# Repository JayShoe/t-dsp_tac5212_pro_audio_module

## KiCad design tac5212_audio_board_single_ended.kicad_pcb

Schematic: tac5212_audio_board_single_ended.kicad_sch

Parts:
3V108, 5V108: jumper; jumper_slice_1mm; not fitted
ADD108: 0x50 | 0xA0; SolderJumper-2_Open_Pad0.5x1.0mm_ADDR; not fitted
ADD110: 0x52 | 0xA4; SolderJumper-2_Open_Pad0.5x1.0mm_ADDR; not fitted
ADD111: 0x53 | 0xA6; SolderJumper-2_Open_Pad0.5x1.0mm_ADDR; not fitted
ADD112: 0x51 | 0xA2; SolderJumper-2_Open_Pad0.5x1.0mm_ADDR; not fitted
C108, C111, C115: 10uF; C_0805_2012Metric_Pad1.18x1.45mm_HandSolder; LCSC C2182156
C109, C112, C116: 0.1uF; C_0402_1005Metric; LCSC C106994
C110, C117, C121, C123: 47uF; CP_EIA-3528-21_Kemet-B_Pad1.50x2.35mm_HandSolder; LCSC C284844; not fitted
C113, C114, C120, C122: 0.0047µF (4.7nF); C_0603_1608Metric_Pad1.08x0.95mm_HandSolder; LCSC C1870901
C118, C119, C128: 1uF; C_0603_1608Metric_Pad1.08x0.95mm_HandSolder; LCSC C2172920
C124: 10UF confirm polarity; C_0603_1608Metric_Pad1.08x0.95mm_HandSolder; LCSC C2167896
C125, C126, C127: 10UF; C_0603_1608Metric_Pad1.08x0.95mm_HandSolder; LCSC C2167896
C129: 1uF (IS THIS TOO MUCH?); C_0603_1608Metric_Pad1.08x0.95mm_HandSolder; LCSC C2172920
C130, C131: 47uF; C_0805_2012Metric_Pad1.15x1.40mm_HandSolder; LCSC C16780
D108, D109, D110, D111, D112: TPD1E10B06; D_0402_1005Metric_Pad0.77x0.64mm_HandSolder; LCSC C48260
D113, D114, D115: TPD1E1B04 - 0402 size; D_0402_1005Metric_Pad0.77x0.64mm_HandSolder; LCSC C48260
D116: RED LED; D_0805_2012Metric_custom; LCSC C94868
DOUT108: Jump DOUT1; jumper_slice_disconnected_alt-text; not fitted
E108, E109: jumper; jumper_slice; not fitted
FB108, FB109, FB110, FB111: BLM21A601S - BLM21AG601SH1; C_0805_2012Metric_Pad1.18x1.45mm_HandSolder_alt_location; LCSC C437406
G108, G109, G110, G111, G112, G113, G114, G115, G116: VIA; via; not fitted
G117, G118: jumper; jumper_slice; not fitted
G119: jumper; jumper_slice_alt1; not fitted
GND108: BRIDGE; jumper_slice; not fitted
MCLK108: jumper; SolderJumper-2_P1.3mm_Open_Pad1.0x1.5mm; not fitted
NT108, NT109: NetTie_2; NetTie-2_SMD_Pad0.2mm
PU_EN108: JUMPER; SolderJumper-2_Open_Pad0.5x1.0mm_PU; not fitted
R108, R111, R132, R135: 10 ohm; C_0603_1608Metric_Pad1.08x0.95mm_HandSolder
R109, R127, R131, R134: DNP; C_0603_1608Metric_Pad1.08x0.95mm_HandSolder; not fitted
R110, R112, R113, R114, R115, R118, R119: 0 Ohm; R_0402_1005Metric_Pad0.72x0.64mm_HandSolder; LCSC C242160
R116, R129, R133, R136: 0 ohm; C_0603_1608Metric_Pad1.08x0.95mm_HandSolder
R117, R125: 27 ohm; R_0402_1005Metric_Pad0.72x0.64mm_HandSolder
R120, R121, R128: 2.21k ohm; R_0402_1005Metric; LCSC C138019
R122: 22.0k; R_0402_1005Metric; LCSC C82868
R123, R124: 4.7k; R_0402_1005Metric; LCSC C278641
R126: 2.21k ohm; R_0402_1005Metric; LCSC C60491
R130, R137, R138, R139: 100K; C_0603_1608Metric_Pad1.08x0.95mm_HandSolder
SCL108: jumper; jumper_slice; not fitted
SCL109: jumper; R_0402_1005Metric_Pad0.72x0.64mm_HandSolder; not fitted
SDA108: jumper; jumper_slice; not fitted
T108, T109, T110, T111: Tab
T*C108, T*C110: 10uF; C_0805_2012Metric_Pad1.18x1.45mm_HandSolder; LCSC C2182156
T*C109: 1uF; C_0603_1608Metric_Pad1.08x0.95mm_HandSolder; LCSC C2172920
TAC108-Q1: TAC5212-Q1; Texas_RHB0032E_VQFN-32-1EP_5x5mm_P0.5mm_EP3.45x3.45mm_Therm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; not fitted
TAC5212: TAC5212; VQFN-24-1EP_4x4mm_P0.5mm_EP2.45x2.45mm_ThermalVias; LCSC C44853694
U108: Single Buffer with Tri-state Passthru - SN74LVC1G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; SOT-23-5
U109: 3.3v LDO - TLV74133PDBVR; SOT-23-5; LCSC C471862
board_outline108: board; audio_module_board_outline_50x34.5_d1; not fitted

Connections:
3.3V_A: 3V108.2, T*C110.1, U109.5 (OUT)
3.3V_LDO: 3V108.1, NT109.1, R122.2, R123.2, R126.1, board_outline108.46 (3.3V)
3.3V_THIN: C108.1, C109.1, NT109.2, TAC108-Q1.31 (AVDD), TAC5212.23 (AVDD)
3.3v_IDE: C111.1, C112.1, C128.1, C131.1, PU_EN108.2, SCL109.2, TAC108-Q1.7 (IOVDD), TAC5212.6 (IOVDD), U108.4 (OE^), U108.5 (VCC), board_outline108.4 (GNDD)
5V: 5V108.1, C130.1, NT108.1, board_outline108.45 (5V)
5212_BCLK1: R119.1, board_outline108.11 (BCLK)
5212_DIN1: R118.1, board_outline108.7 (DSP_DOUT)
5212_DOUT1: DOUT108.1, R117.1, U108.1 (A)
5212_DOUT1+: DOUT108.2, R125.1, board_outline108.9 (DSP_DIN)
5212_LRCK1: R115.1, board_outline108.13 (LRCK)
5212_MCLK1: MCLK108.1, board_outline108.19 (MCLK)
5212_SCL: R121.1, SCL108.2, TAC108-Q1.9 (SCL), TAC5212.7 (SCL), board_outline108.37 (SCL)
5212_SDA: R120.1, SDA108.2, TAC108-Q1.10 (SDA), TAC5212.8 (SDA), board_outline108.38 (SDA)
DSP_SCL: SCL108.1, board_outline108.17 (SCL)
DSP_SDA: SDA108.1, board_outline108.15 (SDA)
EN_HELD_HIGH: C129.1, R128.1, U109.3 (EN), board_outline108.1 (HELD_HIGH)
Earth: C108.2, C109.2, C113.2, C114.2, C118.2, C119.1, C120.2, C122.2, D108.2 (K), D109.2 (K), D110.2 (K), D111.2 (K), D112.2 (K), D113.2 (K), D114.2 (K), D115.2 (K), E108.1, E109.1, G108.1, G109.1, G110.1, G111.1, G112.1, G113.1, G114.1, G115.1, G116.1, G119.1, GND108.1, R130.2, R137.2, R138.2, R139.2, board_outline108.22 (AGND), board_outline108.24 (AGND), board_outline108.26 (AGND), board_outline108.28 (AGND), board_outline108.30 (AGND), board_outline108.32 (AGND), board_outline108.34 (AGND), board_outline108.36 (AGND)
GNDD: ADD108.1, C111.2, C112.2, C115.2, C116.2, C128.2, C129.2, C130.2, C131.2, D116.1 (K), G117.2, G118.2, GND108.2, R124.2, TAC108-Q1.1 (VSS), TAC108-Q1.8 (IOVSS), TAC108-Q1.15 (BSTVSS), TAC108-Q1.26 (AVSS), TAC108-Q1.33 (VSS), TAC5212.25 (VSS), TAC5212.A1 (VSS), TAC5212.A2 (VSS), TAC5212.A3 (VSS), TAC5212.A4 (VSS), U108.3 (GND), board_outline108.6 (GNDD), board_outline108.8 (GNDD), board_outline108.10 (GNDD), board_outline108.12 (GNDD), board_outline108.14 (GNDD), board_outline108.16 (GNDD), board_outline108.18 (GNDD), board_outline108.20 (GNDD), board_outline108.39 (GNDD), board_outline108.44 (GNDD), board_outline108.47 (GNDD)
GPI1: MCLK108.2, R110.1, board_outline108.43 (GPI1)
GPIO1: R114.1, board_outline108.40 (GPIO1)
GPIO2: R113.1, board_outline108.41 (GPIO2)
GPO1: R112.1, board_outline108.42 (GPO1)
IN1M: C126.2, TAC108-Q1.19 (IN1M), TAC5212.16 (IN1M)
IN1M+: D114.1 (K), FB110.1, board_outline108.31 (IN1M)
IN1P: C127.2, TAC108-Q1.18 (IN1P), TAC5212.15 (IN1P)
IN1P+: D115.1 (K), FB111.1, board_outline108.29 (IN1P)
IN2M: C124.2, TAC108-Q1.21 (IN2M), TAC5212.18 (IN2M)
IN2M+: D112.1 (K), FB108.1, board_outline108.35 (IN2M)
IN2P: C125.2, TAC108-Q1.20 (IN2P), TAC5212.17 (IN2P)
IN2P+: D113.1 (K), FB109.1, board_outline108.33 (IN2P)
MICBIAS: C118.1, TAC108-Q1.17 (MICBIAS), TAC5212.14 (MICBIAS), board_outline108.48 (MIC_BIAS)
unnamed: 5V108.2, board_outline108.3 (5V)
unnamed: ADD110.1, R122.1
unnamed: ADD111.1, R123.1
unnamed: ADD112.1, R124.1
unnamed: C110.1, C113.1, R108.1, R127.1, R129.2
unnamed: C114.1, C117.1, R109.1, R111.1, R116.2
unnamed: C120.1, C121.1, R131.1, R132.1, R133.2
unnamed: C122.1, C123.1, R134.1, R135.1, R136.2
unnamed: C124.1, FB108.2, R130.1
unnamed: C125.1, FB109.2, R137.1
unnamed: C126.1, FB110.2, R138.1
unnamed: C127.1, FB111.2, R139.1
unnamed: D116.2 (A), R126.2
unnamed: E108.2, board_outline108.49 (AGND)
unnamed: E109.2, board_outline108.50 (AGND)
unnamed: G117.1, board_outline108.51 (DGND)
unnamed: G118.1, board_outline108.52 (DGND)
unnamed: PU_EN108.1, R120.2, R121.2
unnamed: R128.2, SCL109.1
unnamed: ADD108.2, ADD110.2, ADD111.2, ADD112.2, TAC108-Q1.22 (ADDRA), TAC5212.13 (ADDR)
unnamed: R119.2, TAC108-Q1.3 (BCLK), TAC5212.2 (BCLK)
unnamed: R118.2, TAC108-Q1.6 (DIN), TAC5212.5 (DIN)
unnamed: R117.2, TAC108-Q1.5 (DOUT), TAC5212.4 (DOUT)
unnamed: C115.1, C116.1, TAC108-Q1.2 (DREG), TAC5212.1 (DREG)
unnamed: R115.2, TAC108-Q1.4 (FSYNC), TAC5212.3 (FSYNC)
unnamed: R110.2, TAC108-Q1.25 (GPI1A), TAC5212.12 (GPI1)
unnamed: R114.2, TAC108-Q1.11 (GPIO1), TAC5212.9 (GPIO1)
unnamed: R113.2, TAC108-Q1.24 (GPI2A), TAC5212.10 (GPIO2)
unnamed: R112.2, TAC108-Q1.23 (GPO1A), TAC5212.11 (GPO1)
unnamed: C119.2, TAC108-Q1.32 (VREF), TAC5212.24 (VREF)
unnamed: R125.2, U108.2 (B)
unnamed: G119.2, T*C108.2, T*C109.2, T*C110.2, U109.2 (GND)
unnamed: NT108.2, T*C108.1, T*C109.1, U109.1 (IN)
OUT1M: TAC108-Q1.27 (OUT1M), TAC5212.19 (OUT1M)
OUT1M+: C110.2, D108.1 (K), R129.1, board_outline108.23 (OUT1M)
OUT1P: R108.2, R109.2, R111.2, R127.2, R131.2, R132.2, R134.2, R135.2, TAC108-Q1.28 (OUT1P), TAC5212.20 (OUT1P)
OUT1P+: C117.2, D109.1 (K), R116.1, board_outline108.21 (OUTP)
OUT2M: TAC108-Q1.30 (OUT2M), TAC5212.22 (OUT2M)
OUT2M+: C123.2, D111.1 (K), R136.1, board_outline108.27 (OUT2M)
OUT2P: TAC108-Q1.29 (OUT2P), TAC5212.21 (OUT2P)
OUT2P+: C121.2, D110.1 (K), R133.1, board_outline108.25 (OUT2P)

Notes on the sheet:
AUDIO FILTERS
TAC5212 AUDIO CODEC
POWER SUPPLY
MODULE IO
# TAC5212 Audio Module - Input/Output Interface Documentation ## Document Control | Version | Date | Author | Changes | |---------|------|--------|---------| | 1.0 | [Date] | [Name] | Initial release | --- ## Module Overview The TAC5212 audio module provides flexible, high-quality audio input and o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
REPLACE WITH ANALOG BUFFER SUCH AS SN74LVC1G66 SO THERE IS NO CONTENTION BETWEEN THE SUB-MODULES!
DATA OUTPUT BUFFER
TAC5212 AUDIO BREAKOUT MODULE
POWER INDICATOR

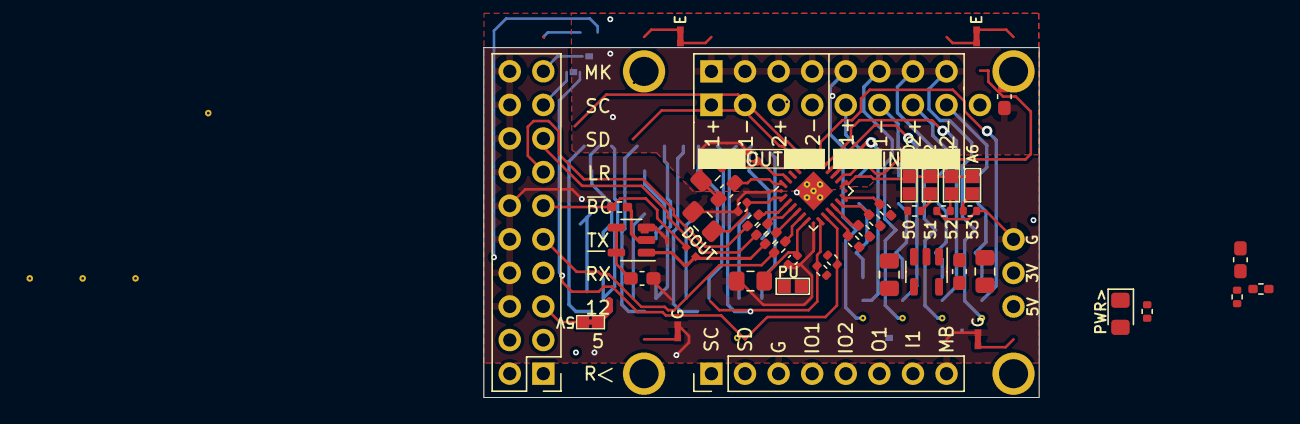
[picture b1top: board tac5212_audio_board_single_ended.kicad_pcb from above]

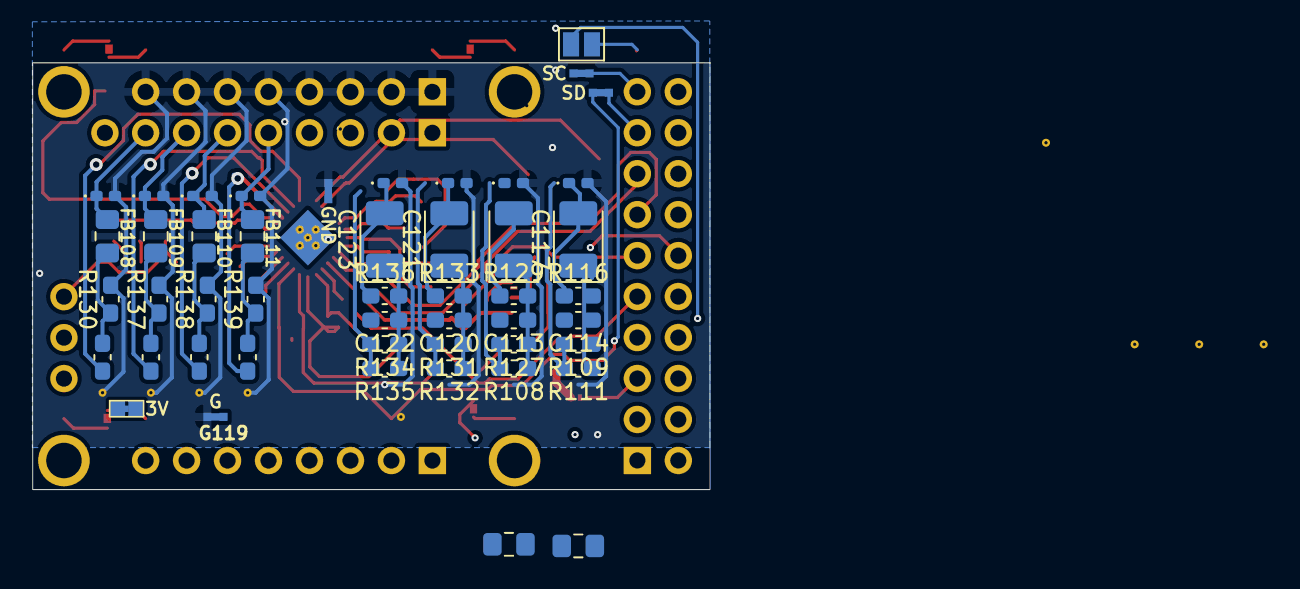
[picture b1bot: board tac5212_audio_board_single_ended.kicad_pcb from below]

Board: 4 copper layers, 42.0 x 26.5 mm, 109 parts (48 on the bottom side), 69 nets.

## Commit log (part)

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2024-08-25 added enable (held-high)
2024-12-24 2024-12-23_T-DSP_TAC5212_V0.5.1
2024-12-24 2024-12-23_T-DSP_TAC5212_V0.5.12
2025-01-06 update after a few builds.
    The 3.3v pin on the T-DSP connector is incorrect.
2025-01-07 update the module io for the 3v from digital audio board v1
2025-04-21 adding documentation
2025-04-21 finish wqfn
2025-08-20 fix net ties and 28 pin wqfn-28
2025-08-20 create fabrication outputs
2025-08-20 working on production
2025-08-20 update fab
2025-08-21 fab update
2026-02-07 Update README: clarify module form factor and backplane integration
2026-02-08 planing for kibot
2026-02-09 fix all drc errors.
2026-02-09 Add KiBot CI/CD pipeline for JLCPCB manufacturing files
    - Add .kibot.yaml config for gerbers, drill, BOM, CPL, and ZIP output
    - Add GitHub Actions workflow triggered on push to main and manual dispatch
    - Add release job to attach JLCPCB ZIP to GitHub Releases on version tags
    - Fix malformed reference designators (5V108, 3V108) that blocked KiBot BOM/CPL
    - Add local build instructions to README
2026-02-09 Fix Package field conflicts and enable gerber job file
    - C128: Package C0603 → C0402 (matches footprint)
    - C124: Package C0805 → C0603 (matches footprint)
    - Enable gerber job file for automatic layer identification by fabs
